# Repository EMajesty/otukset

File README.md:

# Otukset

## Build/Flash

```sh
idf.py set-target esp32c5
idf.py build
idf.py -p /dev/ttyUSB0 flash monitor
```

||||||
|---|---|---|---|---|
||ESP32-C5||||
||240x320 ST7789||||
||BMI160||||
||GROW GM803|||[Datasheet](https://www.dropbox.com/scl/fo/87hz5h82k25j3p9k5u603/ADiCjYV0TvDI0lTbUVLTUDI/GM803%20Series%20Barcode%20reader%20module%20User%20Manual-V1.2.4/GM803%20Series%20Barcode%20reader%20module%20User%20Manual-V1.2.4.pdf)|

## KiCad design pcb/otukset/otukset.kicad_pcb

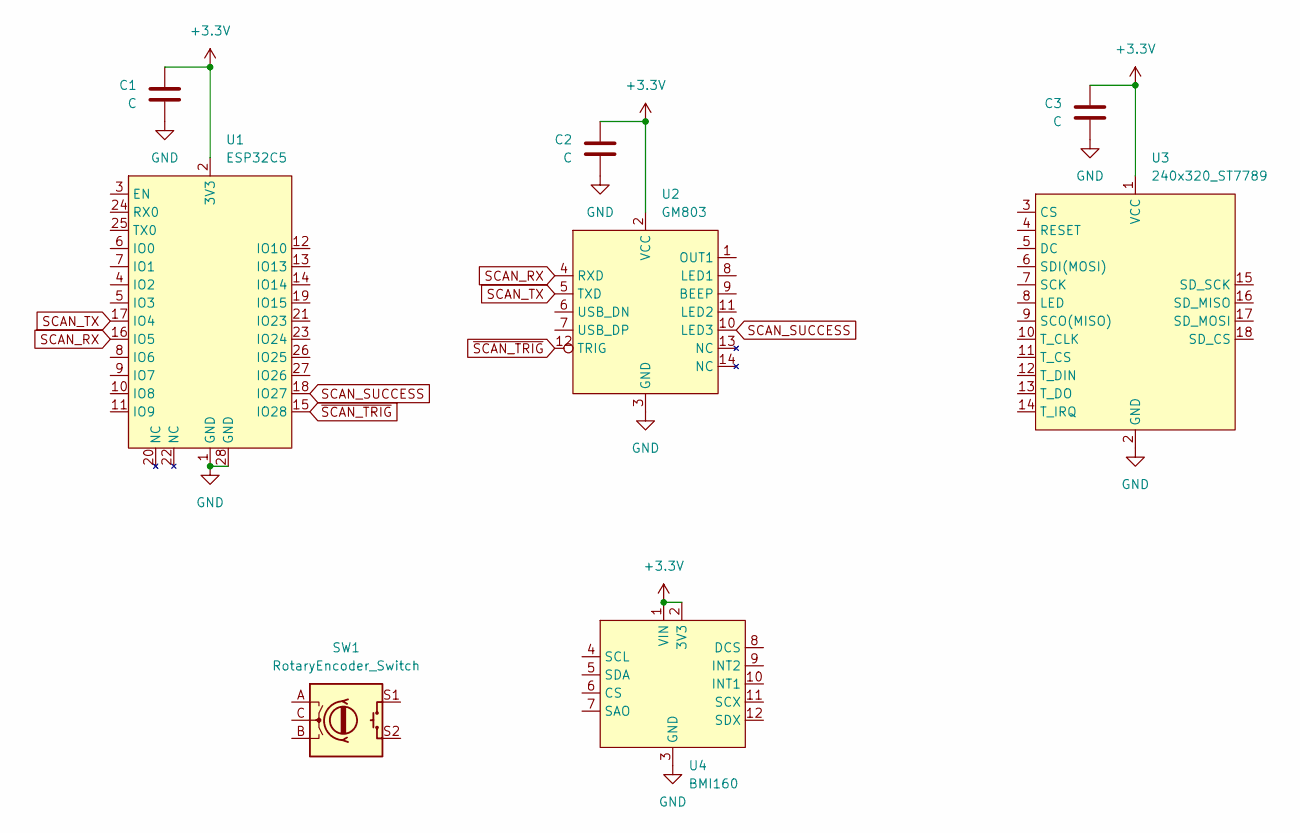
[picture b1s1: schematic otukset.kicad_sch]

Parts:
C1, C2, C3: C; C_0805_2012Metric
SW1: RotaryEncoder_Switch; EC11_Horizontal
U1: ESP32C5
U2: GM803
U3: 240x320_ST7789; 240x320_ST7789_2.8
U4: BMI160

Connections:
+3.3V: C1.1, C2.1, C3.1, U1.2 (3V3), U2.2 (VCC), U3.1 (VCC), U4.1 (VIN), U4.2 (3V3)
GND: C1.2, C2.2, C3.2, U1.1 (GND), U1.28 (GND), U2.3 (GND), U3.2 (GND), U4.3 (GND)
SCAN_RX: U1.16 (IO5), U2.4 (RXD)
SCAN_SUCCESS: U1.18 (IO27), U2.10 (LED3)
SCAN_TX: U1.17 (IO4), U2.5 (TXD)
~SCAN_TRIG: U1.15 (IO28), U2.12 (TRIG)

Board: 2 copper layers, 8 parts (6 on the bottom side), 6 nets, no tracks yet.

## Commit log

2026-02-13 init
2026-02-13 giga vibe
2026-03-04 stuff
